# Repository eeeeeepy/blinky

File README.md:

# blinky
Little name badge sized PCB to make LEDs go blinky, using an ATTINY13A and a CR2032 battery.  

My first proper microcontroller and PCB design, made for a convention that I ended up not attending. Hopefully it can be of use to others out there.  

You can get this badge made and assembled by PCBWay [here](https://www.pcbway.com/project/shareproject/blink_y_badge_168d32d1.html)!

## Programming

I use a 6 pin, 1,27mm pitch pogo pin adapter like [this](https://pl.aliexpress.com/item/1005005732753061.html) for programming. You could also solder wires to the pads, or use something else with the same pitch. Any ISP programmer, such as USBASP or Arduino as ISP should work.

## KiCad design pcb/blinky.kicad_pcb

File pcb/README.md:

# pcb
PCB for the blinky project.

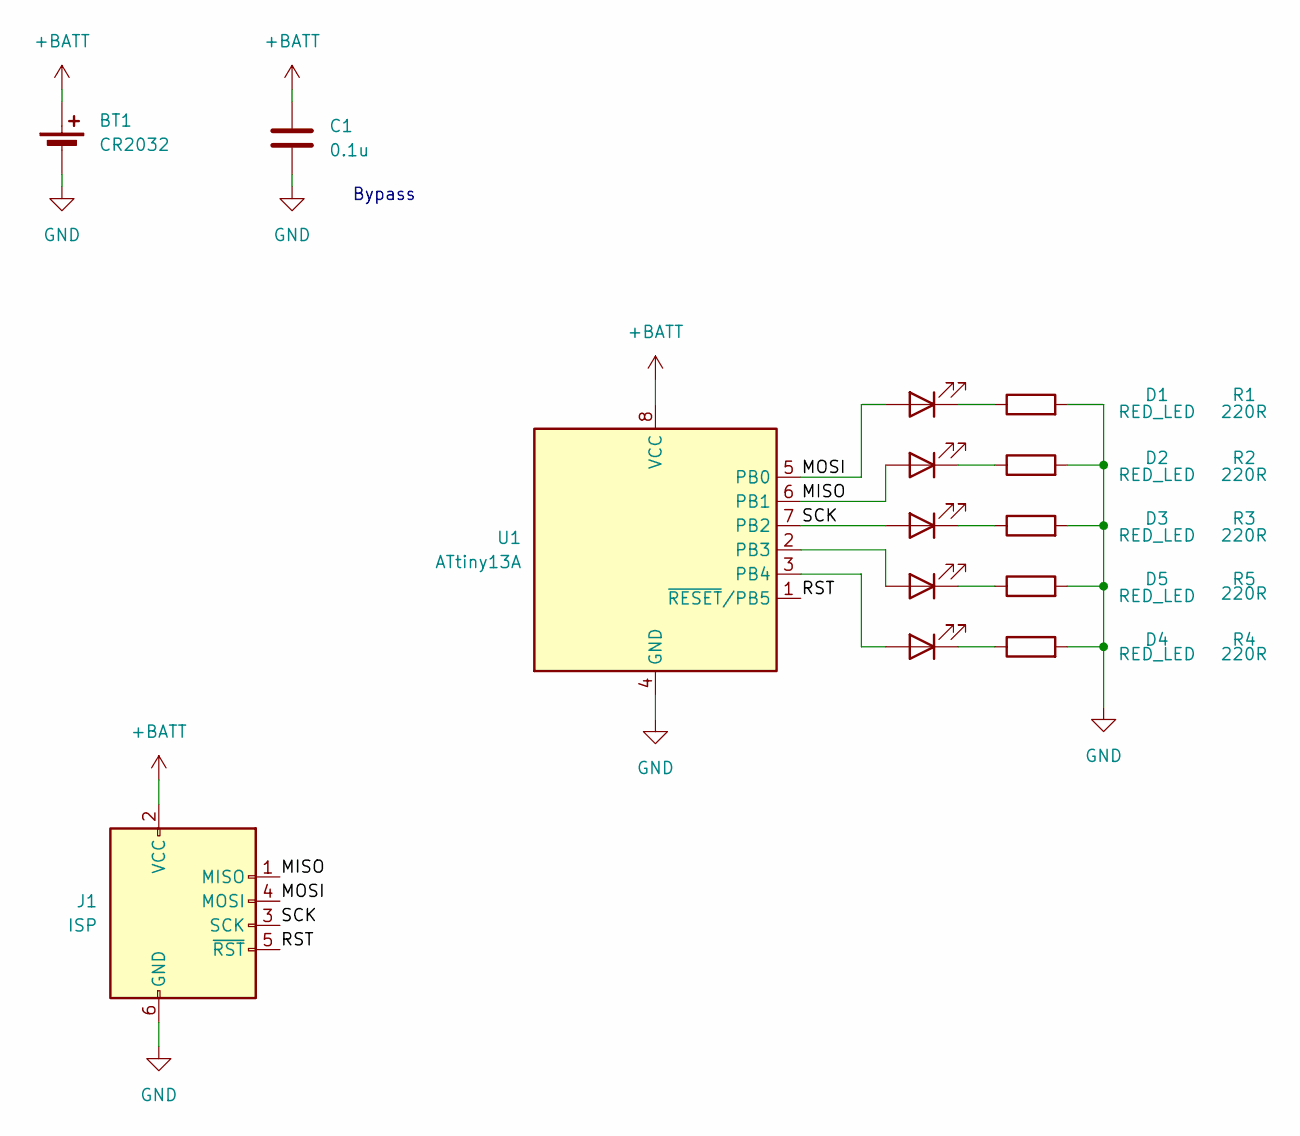
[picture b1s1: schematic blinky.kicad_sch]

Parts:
BT1: CR2032; BatteryHolder_Multicomp_BC-2001_1x2032; LCSC C70373
C1: 0.1u; C_0805_2012Metric_Pad1.18x1.45mm_HandSolder; LCSC C476766
D1, D2, D3, D4, D5: RED_LED; LED_0805_2012Metric_Pad1.15x1.40mm_HandSolder; LCSC C965812
J1: ISP; 06x1_1.27mm
R1, R2, R3, R4, R5: 220R; R_0805_2012Metric_Pad1.20x1.40mm_HandSolder; LCSC C2933537
U1: ATtiny13A; SOIC-8_3.9x4.9mm_P1.27mm; LCSC C40382

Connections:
+BATT: BT1.1 (+), C1.1, J1.2 (VCC), U1.8 (VCC)
/MISO: D2.2 (A), J1.1 (MISO), U1.6 (PB1)
/MOSI: D1.2 (A), J1.4 (MOSI), U1.5 (PB0)
/RST: J1.5 (~RST), U1.1 (~RESET/PB5)
/SCK: D3.2 (A), J1.3 (SCK), U1.7 (PB2)
GND: BT1.2 (-), C1.2, J1.6 (GND), R1.2, R2.2, R3.2, R4.2, R5.2, U1.4 (GND)
unnamed: D1.1 (K), R1.1
unnamed: D2.1 (K), R2.1
unnamed: D3.1 (K), R3.1
unnamed: D4.2 (A), U1.3 (PB4)
unnamed: D4.1 (K), R4.1
unnamed: D5.2 (A), U1.2 (PB3)
unnamed: D5.1 (K), R5.1

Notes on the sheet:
Bypass

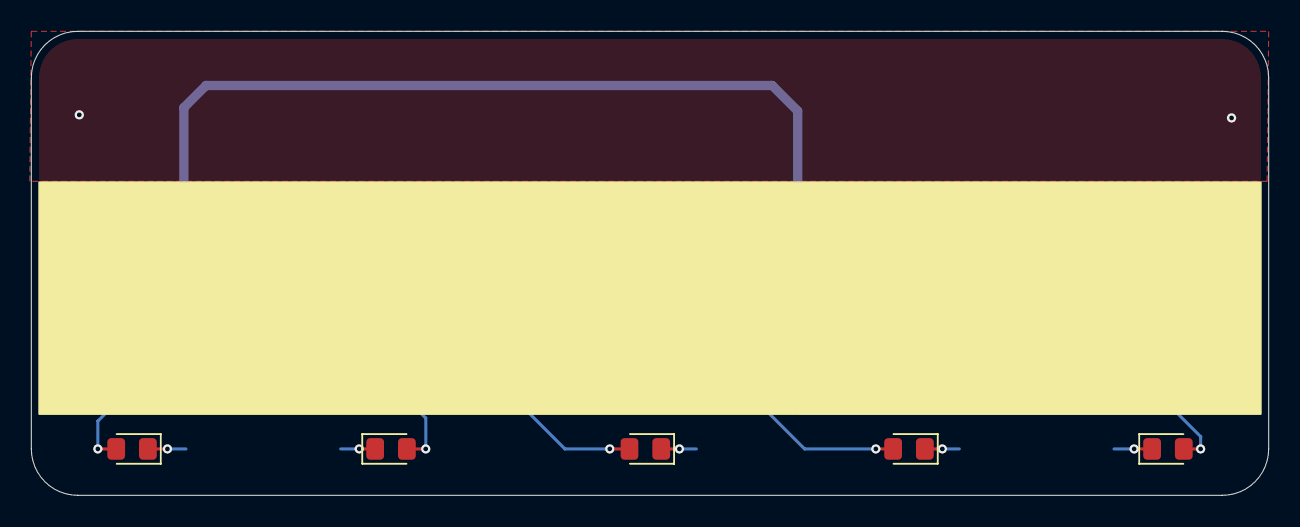
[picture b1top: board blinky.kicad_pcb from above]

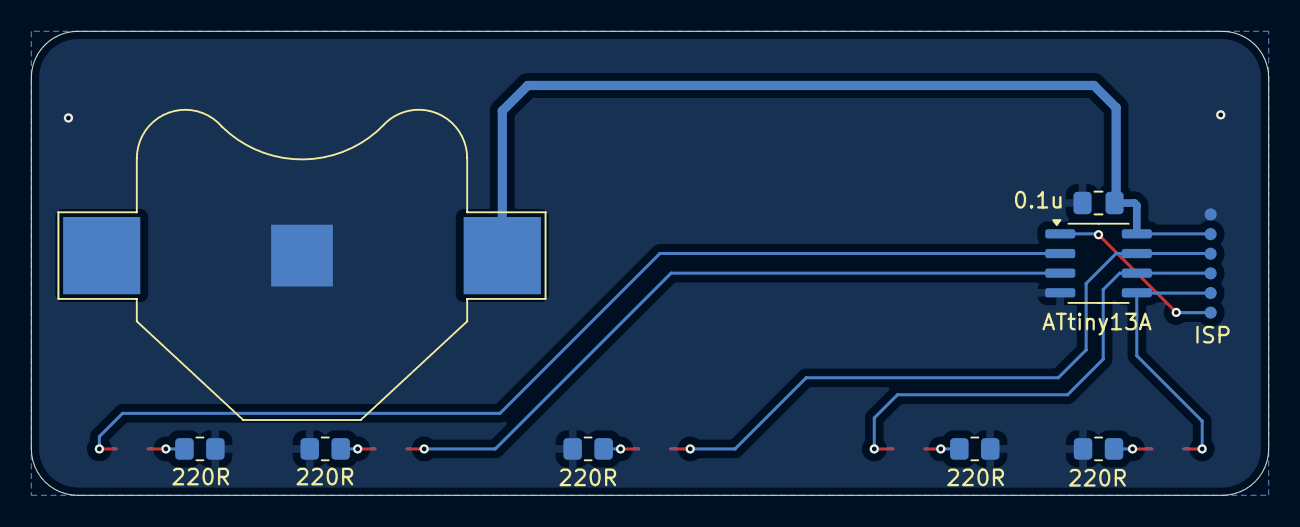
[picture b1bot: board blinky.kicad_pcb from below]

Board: 2 copper layers, 80.0 x 30.0 mm, 14 parts (9 on the bottom side), 13 nets.

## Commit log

2024-08-11 Update README.md and add pics
2024-08-11 Add website link to PCB
2024-08-11 Add ISP header and LCSC part no.
2024-09-18 Code rewrite
2024-09-21 Create LICENSE
2024-12-04 Move code to Arduino IDE
2024-12-27 Move to Makefile for code
2024-12-27 Change font on PCB and remove dead site link
2024-12-27 Add VSCode config
2024-12-27 Add VSCode entries to .gitignore
2025-05-22 Clean up
